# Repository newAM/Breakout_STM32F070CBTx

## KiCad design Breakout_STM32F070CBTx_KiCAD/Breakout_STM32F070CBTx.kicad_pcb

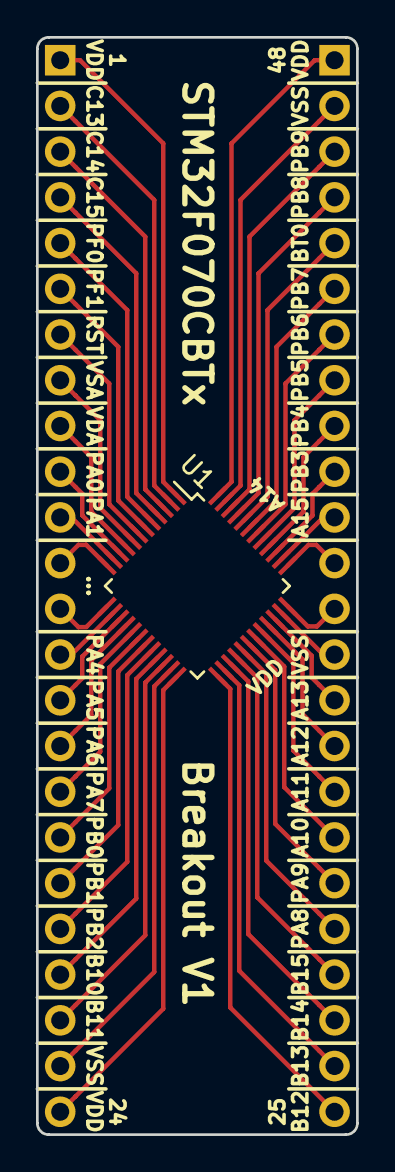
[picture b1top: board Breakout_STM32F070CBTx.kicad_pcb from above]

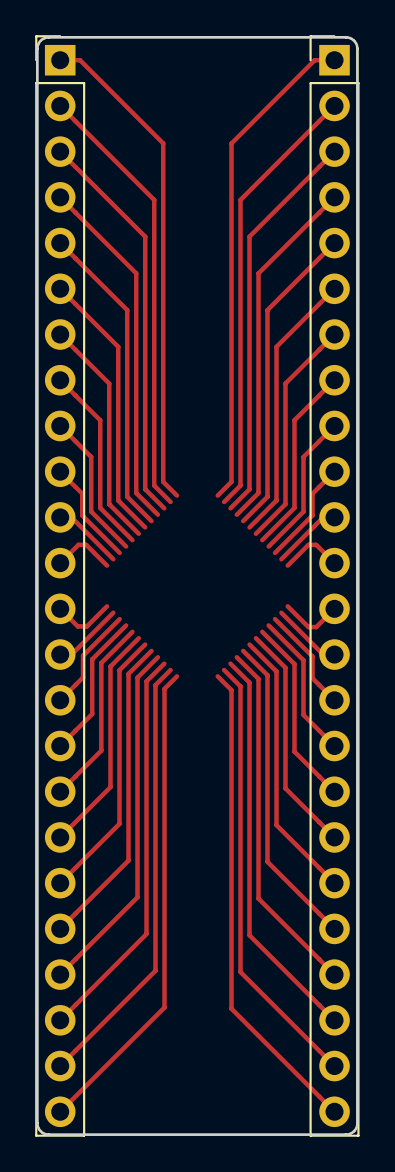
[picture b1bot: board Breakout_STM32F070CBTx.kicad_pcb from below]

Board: 2 copper layers, 17.8 x 61.0 mm, 3 parts (2 on the bottom side), 48 nets.

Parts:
U1: STM32F070CBTx; LQFP-48_7x7mm_Pitch0.5mm
X1, X2: Conn_01x24; Pin_Header_Straight_1x24_Pitch2.54mm

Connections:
1: U1.1, X1.1
2: U1.2, X1.2
3: U1.3, X1.3
4: U1.4, X1.4
5: U1.5, X1.5
6: U1.6, X1.6
7: U1.7, X1.7
8: U1.8, X1.8
9: U1.9, X1.9
10: U1.10, X1.10
11: U1.11, X1.11
12: U1.12, X1.12
13: U1.13, X1.13
14: U1.14, X1.14
15: U1.15, X1.15
16: U1.16, X1.16
17: U1.17, X1.17
18: U1.18, X1.18
19: U1.19, X1.19
20: U1.20, X1.20
21: U1.21, X1.21
22: U1.22, X1.22
23: U1.23, X1.23
24: U1.24, X1.24
25: U1.25, X2.24
26: U1.26, X2.23
27: U1.27, X2.22
28: U1.28, X2.21
29: U1.29, X2.20
30: U1.30, X2.19
31: U1.31, X2.18
32: U1.32, X2.17
33: U1.33, X2.16
34: U1.34, X2.15
35: U1.35, X2.14
36: U1.36, X2.13
37: U1.37, X2.12
38: U1.38, X2.11
39: U1.39, X2.10
40: U1.40, X2.9
41: U1.41, X2.8
42: U1.42, X2.7
43: U1.43, X2.6
44: U1.44, X2.5
45: U1.45, X2.4
46: U1.46, X2.3
47: U1.47, X2.2
48: U1.48, X2.1

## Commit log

2018-09-15 initial commit, V1 complete
